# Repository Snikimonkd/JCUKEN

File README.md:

# JCUKEN

Cyrillic-friendly low profile ortholinear split keyboard.

## Tools

Designed with [ergogen](https://github.com/ergogen/ergogen).

Routed with [KiCad](https://www.kicad.org/).

## Version 1

### Top view

### Close up view

### High stands

### Low stands

## Materials

| Part                      | Link                                                                        | Price                     |
| ------------------------- | --------------------------------------------------------------------------- | ------------------------- |
| PCB (5 pcs)               | [link](https://aliexpress.ru/store/1100324072?g=y&page=1&searchInfo=search) | 25$                       |
| ProMicro (2 pcs)          | [link](https://aliexpress.ru/item/1005005787284179.html)                    | 5$                        |
| Diods (100 pcs)           | [link](https://aliexpress.ru/item/1005006043982096.html)                    | 1$                        |
| Reset buttons (100 pcs)   | [link](https://aliexpress.ru/item/4000533166385.html)                       | 1$                        |
| TRRS cable                | [link](https://aliexpress.ru/item/1005003415667083.html)                    | 2$                        |
| Switches (70 pcs)         | [link](https://aliexpress.ru/item/1005005883472162.html)                    | 27$                       |
| TRRS connectors (10 pcs)  | [link](https://aliexpress.ru/item/1005003299392377.html)                    | 1$                        |
| Hot swap sockets (70 pcs) | [link](https://aliexpress.ru/item/1005006007846154.html)                    | 10$                       |
| Keycaps (50pcs)           | [link](https://aliexpress.ru/item/1005004558099208.html)                    | 22$                       |
| Case                      | [link](https://github.com/Snikimonkd/JCUKEN/tree/main/case)                 | 2$ (3 beers for my buddy) |
| Bolts/Stands (10 pcs)     | Local hardware store                                                        | 1$                        |
| **Total**                 |                                                                             | **~97$**                  |

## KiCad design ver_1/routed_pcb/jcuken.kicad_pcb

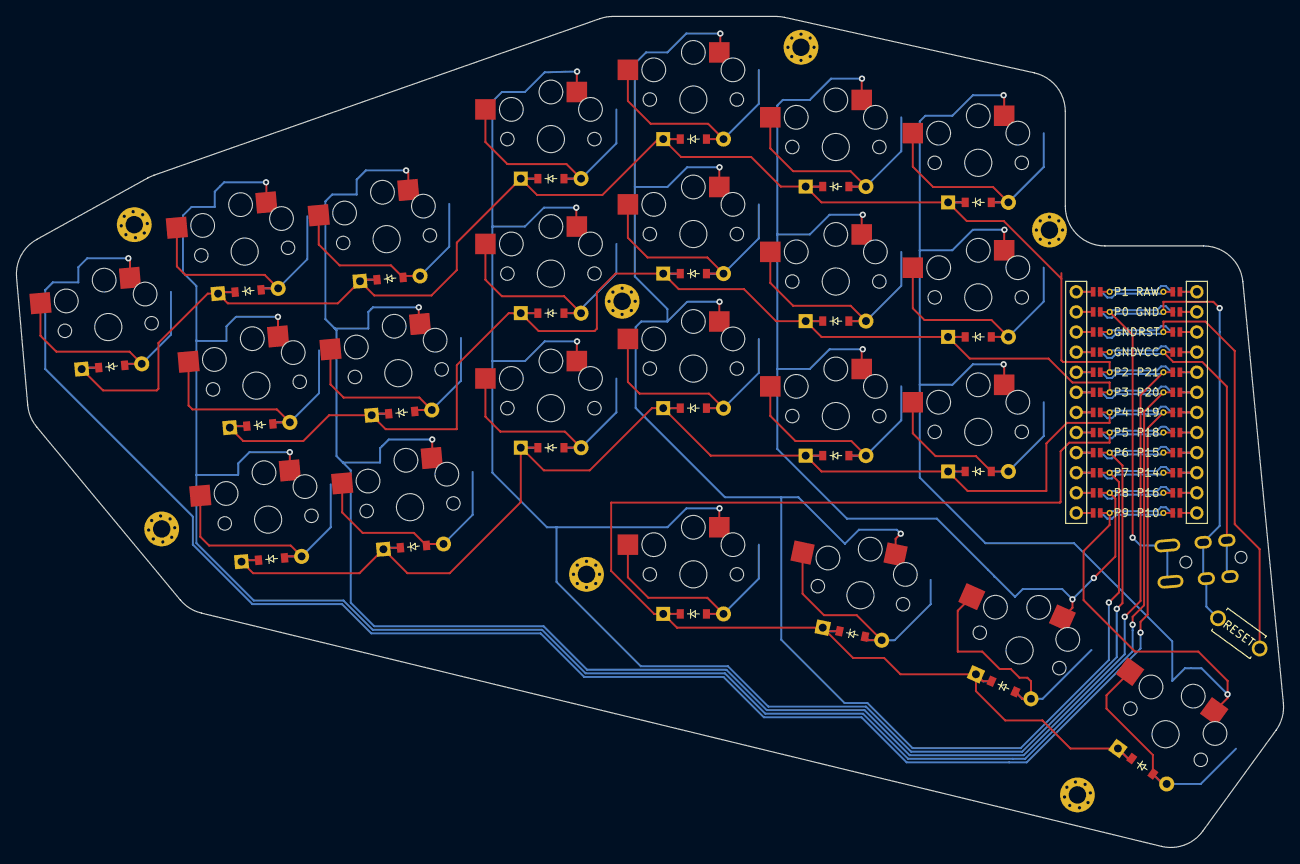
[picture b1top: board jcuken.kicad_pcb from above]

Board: 2 copper layers, 160.1 x 105.0 mm, 56 parts (0 on the bottom side), 50 nets.

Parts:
B1: ResetSW
D1, D2, D3, D4, D5, D6, D7, D8, D9, D10, D11, D12, D13, D14, D15, D16, D17, D18, D19, D20, D21, D22, D23: ComboDiode
MCU1: nice_nano
S1, S2, S3, S4, S5, S6, S7, S8, S9, S10, S11, S12, S13, S14, S15, S16, S17, S18, S19, S20, S21, S22, S23: PG1350
TRRS1: TRRS-PJ-320A-dual; trrs_pj320a (reversible, symmetric)
_1, _2, _3, _4, _5, _6, _7: MountingHole_2.2mm_M2_Pad_Via

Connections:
GND: B1.2, MCU1.2, TRRS1.2
MCU1_1: MCU1.1, MCU1.24
MCU1_2: MCU1.2, MCU1.23
MCU1_3: MCU1.3, MCU1.22
MCU1_4: MCU1.4, MCU1.21
MCU1_5: MCU1.5, MCU1.20
MCU1_6: MCU1.6, MCU1.19
MCU1_7: MCU1.7, MCU1.18
MCU1_8: MCU1.8, MCU1.17
MCU1_9: MCU1.9, MCU1.16
MCU1_10: MCU1.10, MCU1.15
MCU1_11: MCU1.11, MCU1.14
MCU1_12: MCU1.12, MCU1.13
P0: MCU1.123, TRRS1.1
P2: D1.1, D4.1, D7.1, D10.1, D13.1, D16.1, D19.1, MCU1.120
P3: D3.1, D6.1, D9.1, D12.1, D15.1, D18.1, MCU1.119
P4: D2.1, D5.1, D8.1, D11.1, D14.1, D17.1, MCU1.118
P5: D20.1, D21.1, D22.1, D23.1, MCU1.117
P6: MCU1.116, S8.1, S9.1, S10.1, S20.1
P7: MCU1.115, S11.1, S12.1, S13.1, S21.1
P8: MCU1.114, S14.1, S15.1, S16.1, S22.1
P9: MCU1.113, S17.1, S18.1, S19.1, S23.1
P19: MCU1.7, S1.1
P20: MCU1.6, S2.1, S3.1, S4.1
P21: MCU1.5, S5.1, S6.1, S7.1
RST: B1.1, MCU1.3
VCC: MCU1.4, TRRS1.3
far_outer_top: D1.2, S1.2
far_thumb: D23.2, S23.2
home_thumb: D21.2, S21.2
index_bottom: D14.2, S14.2
index_home: D15.2, S15.2
index_top: D16.2, S16.2
inner_bottom: D17.2, S17.2
inner_home: D18.2, S18.2
inner_top: D19.2, S19.2
middle_bottom: D11.2, S11.2
middle_home: D12.2, S12.2
middle_top: D13.2, S13.2
near_thumb: D20.2, S20.2
one_more_thumb: D22.2, S22.2
outer_bottom: D2.2, S2.2
outer_home: D3.2, S3.2
outer_top: D4.2, S4.2
pinky_bottom: D5.2, S5.2
pinky_home: D6.2, S6.2
pinky_top: D7.2, S7.2
ring_bottom: D8.2, S8.2
ring_home: D9.2, S9.2
ring_top: D10.2, S10.2

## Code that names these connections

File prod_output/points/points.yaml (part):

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        autobind: 10
        skip: false
        asym: both
        colrow: pinky_bottom
        name: matrix_pinky_bottom
        column_net: P21
        row_net: P4
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        autobind: 10
        skip: false
        asym: both
        colrow: pinky_home
        name: matrix_pinky_home
        column_net: P21
        row_net: P3
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        autobind: 10
        skip: false
        asym: both
        colrow: pinky_top
        name: matrix_pinky_top
        column_net: P21
        row_net: P2
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
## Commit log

2024-02-19 init
2024-03-10 add qmk config
2024-03-10 fix config
2024-03-11 qmk + vial
2024-03-17 clean
2024-03-17 add readme
2024-03-17 move a little bit
2024-03-17 delte useless submodult
2024-03-17 add routed pcb
2024-03-20 add case to readme
2024-03-27 add photos
2024-03-28 add command key
2024-03-28 add backslash and pipe
2024-04-06 version 2 start
2024-04-06 some fixes to v2
2024-04-06 rename a little
2024-04-06 add arc on the right
2024-04-06 make thumb cluster closer
2024-04-06 ittle fix
2024-04-20 change everything
2024-04-20 changed top arc
2024-04-30 make layout less agressive
2024-04-30 fix pcbs
2024-05-11 update footprints + finish board
2024-05-12 update footprints
